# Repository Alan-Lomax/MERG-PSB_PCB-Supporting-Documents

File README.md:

# MERG PCB Supporting Documents

These are the Gerbers and Supporting Files for a MERG Article I wrote on my early experiences with PCB manufacturing.
The main purpose of the article is to describe to other (esp younger) MERG members the process of designing and making up Printed Circuit Boards (PCBs)

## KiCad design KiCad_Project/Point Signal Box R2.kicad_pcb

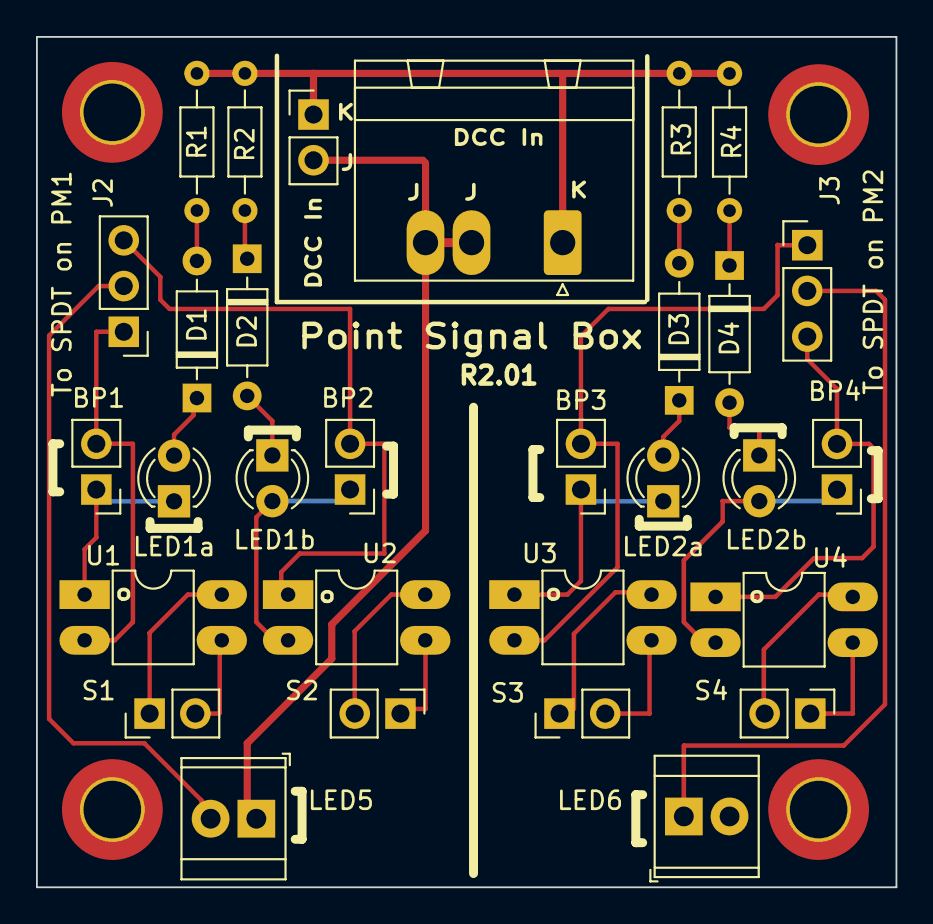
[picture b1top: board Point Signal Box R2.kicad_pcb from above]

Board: 2 copper layers, 47.8 x 47.2 mm, 34 parts (0 on the bottom side), 28 nets.

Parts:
BP1, BP2, BP3, BP4: Bypass; PinHeader_1x02_P2.54mm_Vertical
D1, D2, D3, D4: 1N914; D_DO-35_SOD27_P7.62mm_Horizontal
J1: Alternate DCC; PhoenixContact_GMSTBA_2,5_2-G-7,62_1x02_P7.62mm_Horizontal
J2: To SPDT on PM1; PinHeader_1x03_P2.54mm_Vertical
J3: To SPDT on PM2; PinHeader_1x03_P2.54mm_Vertical
J_DCC1: DCC Input; PinHeader_1x02_P2.54mm_Vertical
LED1: LED1a; LED_D3.0mm
LED2: LED1b; LED_D3.0mm
LED3: LED2a; LED_D3.0mm
LED4: LED2b; LED_D3.0mm
LED5, LED6: To Signal LED; TerminalBlock_TE_282834-2_1x02_P2.54mm_Horizontal
M3, M3#2, M3#3, M3#4: MountingHole_3.2mm_M3_DIN965_Pad_TopBottom
R1, R2, R3, R4: 6.8K; R_Axial_DIN0204_L3.6mm_D1.6mm_P7.62mm_Horizontal
S1, S3: Sw Load 1a; PinHeader_1x02_P2.54mm_Vertical
S2, S4: Sw Load 1b; PinHeader_1x02_P2.54mm_Vertical
U1, U2, U3, U4: TLP241B; DIP-4_W7.62mm_LongPads

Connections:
DCCJ: J1.2, J_DCC1.2, LED5.1, LED6.2
DCCK: J1.1, J_DCC1.1, R1.1, R2.1, R3.1, R4.1
unnamed: BP1.1, LED1.1 (K), U1.1
unnamed: BP1.2, J2.1, U1.2
unnamed: BP2.1, LED2.2 (A), U2.2
unnamed: BP2.2, J2.3, U2.1
unnamed: BP3.1, LED3.1 (K), U3.1
unnamed: BP3.2, J3.1, U3.2
unnamed: BP4.1, LED4.2 (A), U4.2
unnamed: BP4.2, J3.3, U4.1
unnamed: D1.1 (K), LED1.2 (A)
unnamed: D1.2 (A), R1.2
unnamed: D2.1 (K), R2.2
unnamed: D2.2 (A), LED2.1 (K)
unnamed: D3.1 (K), LED3.2 (A)
unnamed: D3.2 (A), R3.2
unnamed: D4.1 (K), R4.2
unnamed: D4.2 (A), LED4.1 (K)
unnamed: J2.2, LED5.2
unnamed: J3.2, LED6.1
unnamed: S1.1, U1.4
unnamed: S1.2, U1.3
unnamed: S2.1, U2.3
unnamed: S2.2, U2.4
unnamed: S3.1, U3.4
unnamed: S3.2, U3.3
unnamed: S4.1, U4.3
unnamed: S4.2, U4.4

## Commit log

2022-11-05 Intitial Upload
    Supporting documents for the MERG article on Printed Circuit Board manufacturing.
    Specifically the Point Signal Box PCB (PSB-PCB)
2022-11-06 Update MERG PSB R2 Build Instructions.docx
    Additional clarity and step numbers to the instructions. Updated photos to match those used in the article.
2022-11-07 Minor update
    PDF Version of Build Instructions
2022-11-07 Removed Backups
    KiCad backups are not needed
2022-11-07 Streamlined the Readme
2022-11-07 Rev 2 Update to Article
    Refactoring of Article - separating out Figures and PowerPoints which are now listed here for the editors benefit.
2022-11-20 Minor updates during editorial process
2022-11-20 Removed KiCad backups
2022-11-20 Touchup of photos
    General cleanup of photos and PowerPoints to improve clarity. Getting ready for publishing.
2022-11-20 Minor Update
    Replaced some images in the build instructions with those used in the article for consistency and clarity.
2022-12-27 Incremental
2025-10-03 fix Typos in file name
2025-10-03 Update README.md
    Fix Typos

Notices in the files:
KiCad_Project/Point Signal Box R2.kicad_pcb:
(c)2022
